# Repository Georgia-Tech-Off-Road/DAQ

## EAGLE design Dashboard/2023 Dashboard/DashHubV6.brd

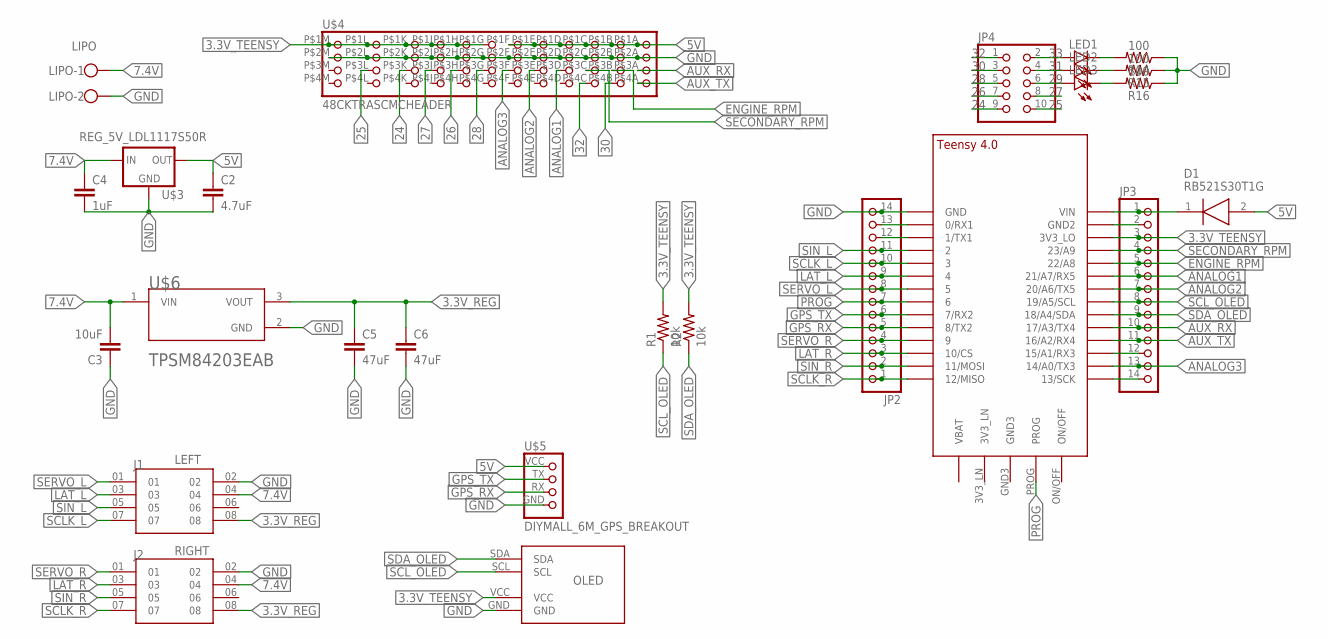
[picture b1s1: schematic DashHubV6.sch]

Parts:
C2: 4.7uF; C0603
C3: 10uF; C1206
C4: 1uF; C1206
C5, C6: 47uF; C1206
D1: RB521S30T1G; SODFL1608X70N
J1: LEFT; SAMTEC_ESW-104-23-L-D
J2: RIGHT; SAMTEC_ESW-104-23-L-D
JP2, JP3: PINHD-1X14; 1X14
JP4: PINHD-2X5; 2X05
LED1, LED2, LED3: LEDCHIPLED_1206; CHIPLED_1206
LIPO: LIPO; W237-102
R1, R2: 10k; R0603
R14, R15, R16: 100; AXIAL-0.3
U$1: TEENSY_4.0-BASIC
U$2: OLED_SSD1306
U$3: REG_5V_LDL1117S50R; SOT230P700X180-4N
U$4: 48CKTRASCMCHEADER
U$5: DIYMALL_6M_GPS_BREAKOUT
U$6: TPSM84205EAB

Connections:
3.3V_REG: C5.1, C6.1, J1.08, J2.08, U$6.3 (VOUT)
3.3V_TEENSY: JP3.3, R1.2, R2.2, U$1.3V3_LO, U$2.VCC, U$4.P$1G (1G), U$4.P$1H (1H), U$4.P$1J (1J), U$4.P$1K (1K), U$4.P$1L (1L), U$4.P$1M (1M)
5V: C2.1, D1.2 (A), U$3.2 (OUT), U$3.4 (OUT), U$4.P$1A (1A), U$4.P$1B (1B), U$4.P$1C (1C), U$4.P$1D (1D), U$4.P$1E (1E), U$4.P$1F (1F), U$5.VCC
7.4V: C3.2, C4.1, J1.04, J2.04, LIPO.1, U$3.3 (IN), U$6.1 (VIN)
24: JP4.9, U$4.P$3K (3K)
25: JP4.10, U$4.P$3L (3L)
26: JP4.7, U$4.P$3H (3H)
27: JP4.8, U$4.P$3J (3J)
28: JP4.5, U$4.P$3G (3G)
29: JP4.6, LED3.A
30: JP4.3, U$4.P$4B (4B)
31: JP4.4, LED2.A
32: JP4.1, U$4.P$4C (4C)
33: JP4.2, LED1.A
ANALOG1: JP3.6, U$1.21/A7 (21/A7/RX5), U$4.P$3D (3D)
ANALOG2: JP3.7, U$1.20/A6 (20/A6/TX5), U$4.P$3E (3E)
ANALOG3: JP3.13, U$1.14/A0 (14/A0/TX3), U$4.P$3F (3F)
AUX_RX: JP3.10, U$1.17/A3 (17/A3/TX4), U$4.P$3A (3A)
AUX_TX: JP3.11, U$1.16/A2 (16/A2/RX4), U$4.P$4A (4A)
CURR_SENSE: JP3.12, U$1.15/A1 (15/A1/RX3)
ENGINE_RPM: JP3.5, U$1.22/A8, U$4.P$3B (3B)
GND: C2.2, C3.1, C4.2, C5.2, C6.2, J1.02, J2.02, JP2.14, LIPO.2, R14.P$1 (1), R15.P$1 (1), R16.P$1 (1), U$1.GND, U$2.GND, U$3.1 (GND), U$4.P$2A (2A), U$4.P$2B (2B), U$4.P$2C (2C), U$4.P$2D (2D), U$4.P$2E (2E), U$4.P$2F (2F), U$4.P$2G (2G), U$4.P$2H (2H), U$4.P$2J (2J), U$4.P$2K (2K), U$4.P$2L (2L), U$4.P$2M (2M), U$5.GND, U$6.2 (GND)
GND2: JP3.2, U$1.GND2
GPS_RX: JP2.5, U$1.8 (8/TX2), U$5.RX
GPS_TX: JP2.6, U$1.7 (7/RX2), U$5.TX
LAT_L: J1.03, JP2.9, U$1.4/CANRX (4)
LAT_R: J2.03, JP2.3, U$1.10/CS
unnamed: D1.1 (K), JP3.1, U$1.VIN
unnamed: LED1.C, R14.P$2 (2)
unnamed: LED2.C, R15.P$2 (2)
unnamed: LED3.C, R16.P$2 (2)
PROG: JP2.7, U$1.6, U$1.PROG
SCLK_D: JP3.14, U$1.13/SCK
SCLK_L: J1.07, JP2.10, U$1.3/CANTX (3)
SCLK_R: J2.07, JP2.1, U$1.12/MISO
SCL_OLED: JP3.8, R1.1, U$1.19/A5/SCL, U$2.SCL
SDA_OLED: JP3.9, R2.1, U$1.18/A4/SDA, U$2.SDA
SECONDARY_RPM: JP3.4, U$1.23/A9, U$4.P$3C (3C)
SERVO_L: J1.01, JP2.8, U$1.5
SERVO_R: J2.01, JP2.4, U$1.9/CS (9)
SIN_L: J1.05, JP2.11, U$1.2
SIN_R: J2.05, JP2.2, U$1.11/MOSI
XBEE_RX: JP2.12, U$1.1/TX (1/TX1)
XBEE_TX: JP2.13, U$1.0/RX (0/RX1)

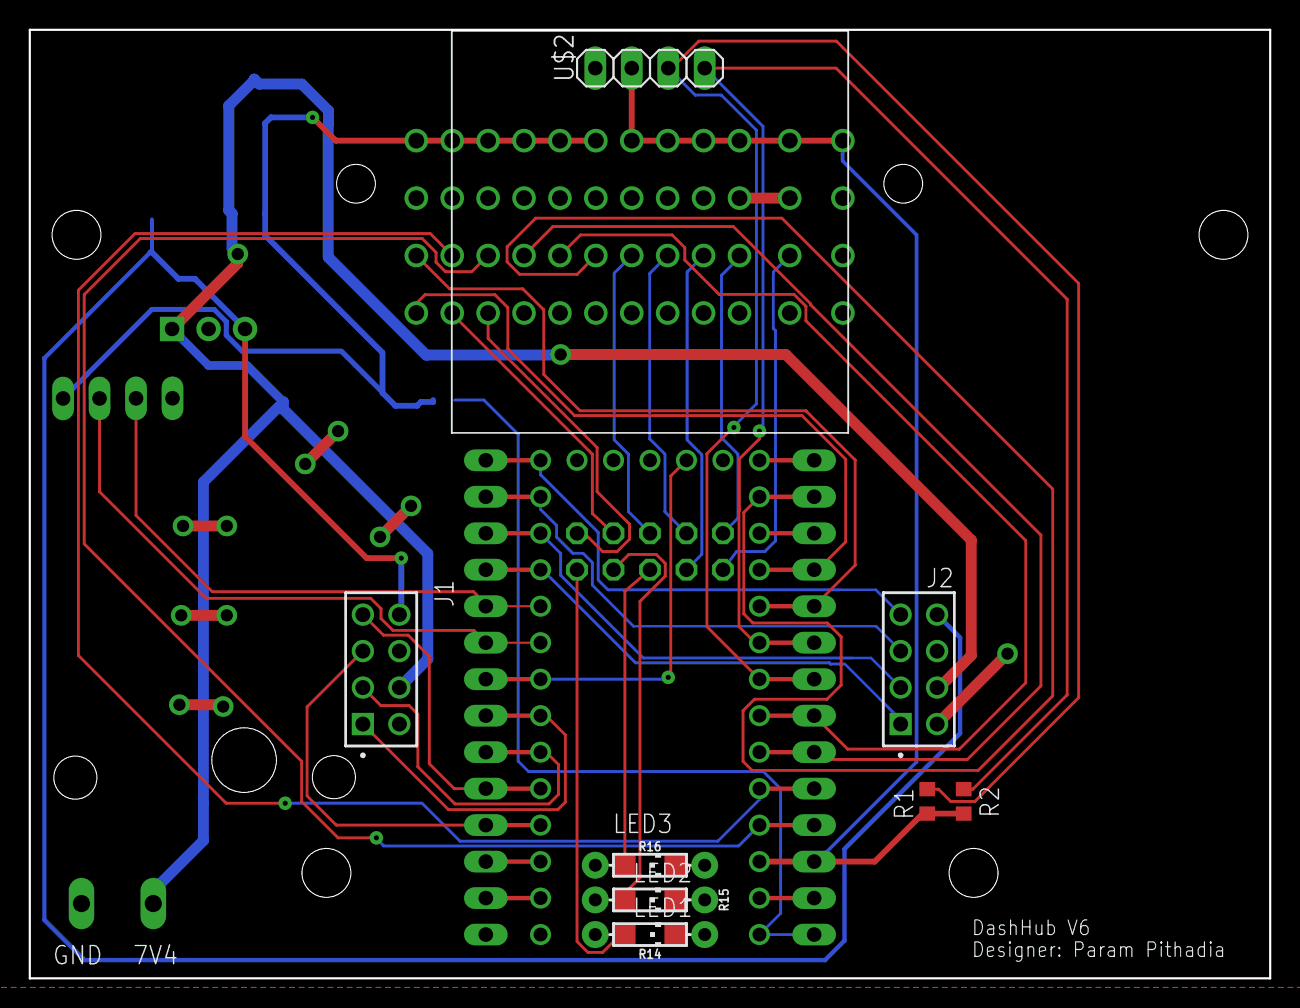
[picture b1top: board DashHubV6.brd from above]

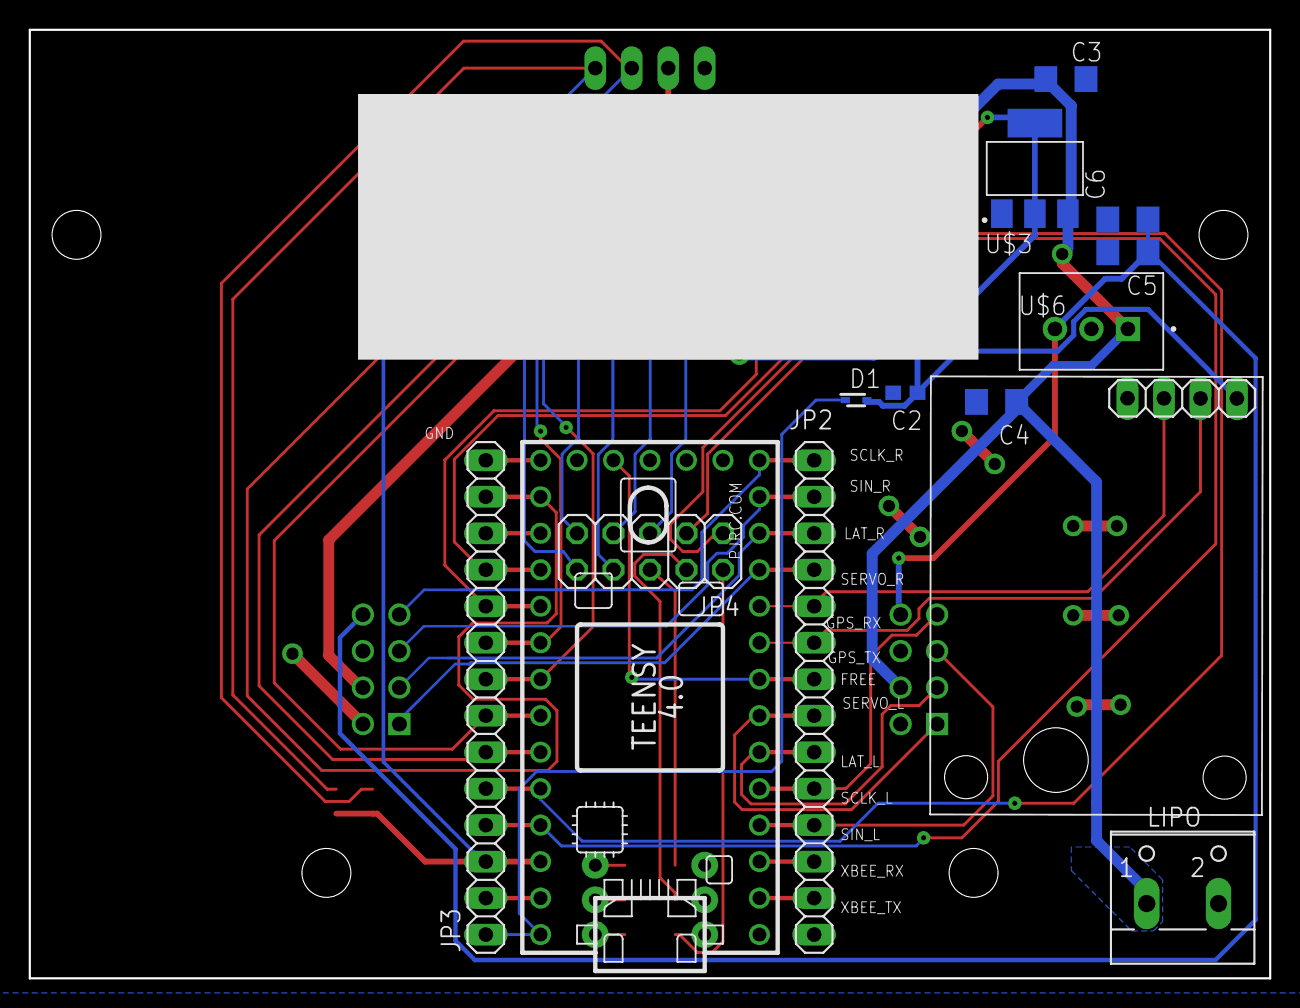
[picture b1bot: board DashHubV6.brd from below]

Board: 2 copper layers, 86.4 x 66.0 mm, 26 parts (15 on the bottom side), 44 nets.

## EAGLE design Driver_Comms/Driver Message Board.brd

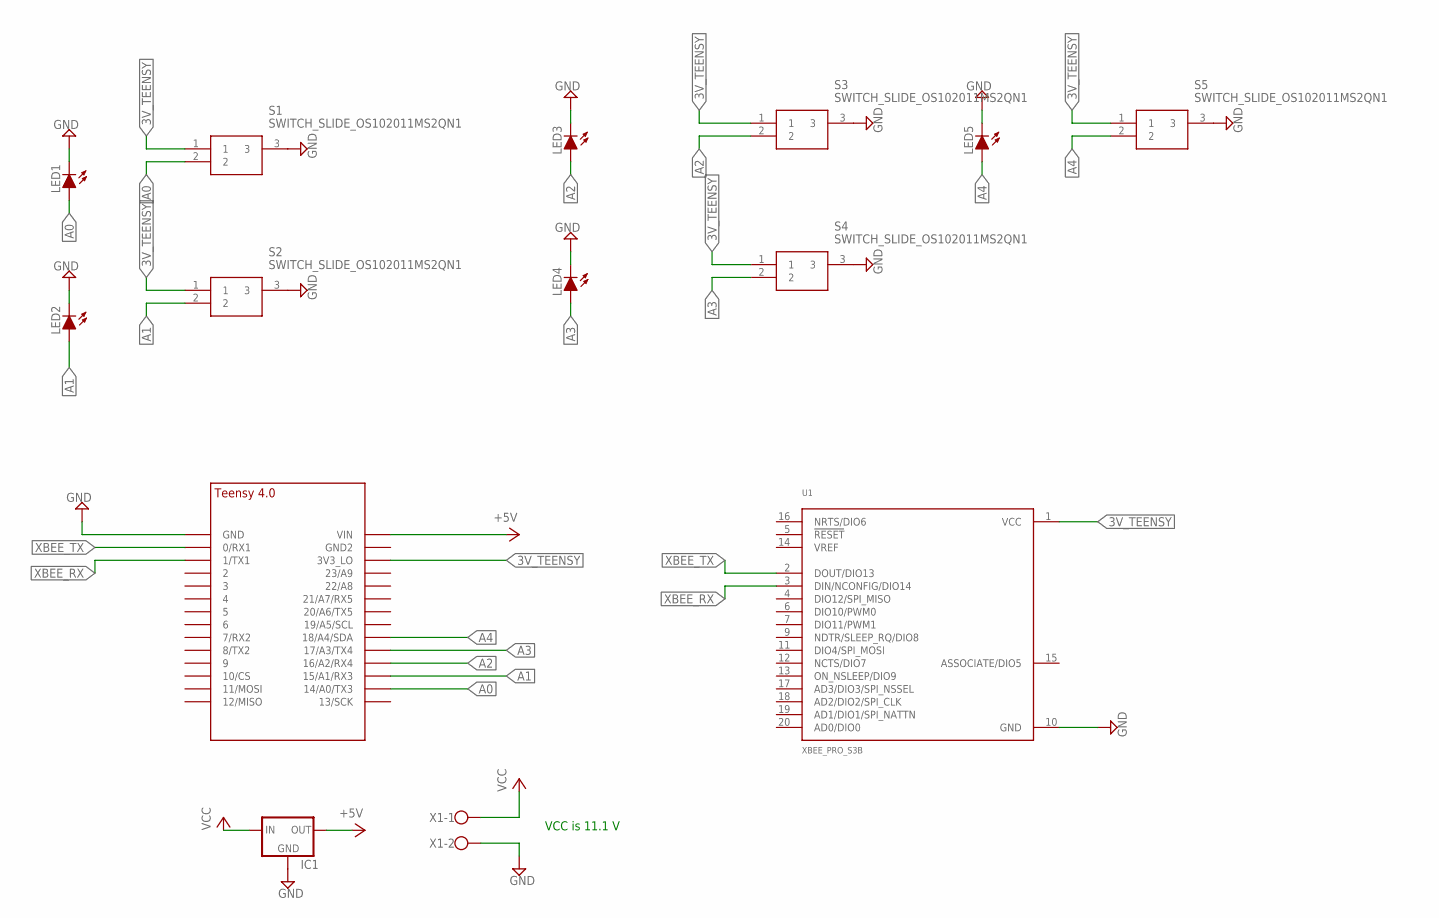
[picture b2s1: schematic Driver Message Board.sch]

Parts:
IC1: REG_5V_L7805_HOR_HOLE; TO-220-H-HOLE
LED1, LED2, LED3, LED4, LED5: LED-5MM
S1, S2, S3, S4, S5: SWITCH_SLIDE_OS102011MS2QN1; OS102011MA1QN1
U1: XBEE_PRO_S3B
U$1: TEENSY_4.0_SIMPLE
X1: W237-102

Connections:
3V_TEENSY: S1.1, S2.1, S3.1, S4.1, S5.1, U1.1 (VCC), U$1.3V3_LO
+5V: IC1.3 (OUT), U$1.VIN
A0: LED1.A, S1.2, U$1.14/A0 (14/A0/TX3)
A1: LED2.A, S2.2, U$1.15/A1 (15/A1/RX3)
A2: LED3.A, S3.2, U$1.16/A2 (16/A2/RX4)
A3: LED4.A, S4.2, U$1.17/A3 (17/A3/TX4)
A4: LED5.A, S5.2, U$1.18/A4/SDA
GND: IC1.2 (GND), LED1.K (C), LED2.K (C), LED3.K (C), LED4.K (C), LED5.K (C), S1.3, S2.3, S3.3, S4.3, S5.3, U1.10 (GND), U$1.GND, X1.2
VCC: IC1.1 (IN), X1.1
XBEE_RX: U1.3 (DIN/NCONFIG/DIO14), U$1.1/TX (1/TX1)
XBEE_TX: U1.2 (DOUT/DIO13), U$1.0/RX (0/RX1)

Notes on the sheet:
VCC is 11.1 V

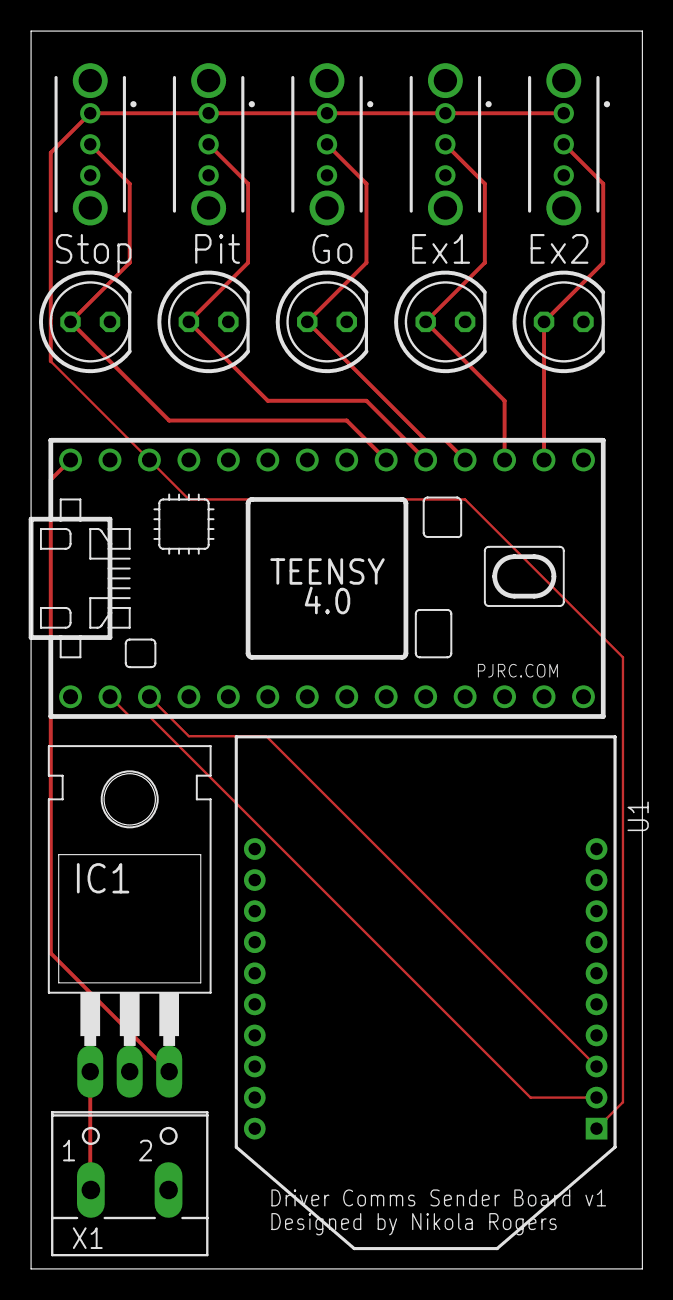
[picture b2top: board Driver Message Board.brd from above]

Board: 2 copper layers, 39.4 x 79.7 mm, 14 parts (0 on the bottom side), 11 nets.

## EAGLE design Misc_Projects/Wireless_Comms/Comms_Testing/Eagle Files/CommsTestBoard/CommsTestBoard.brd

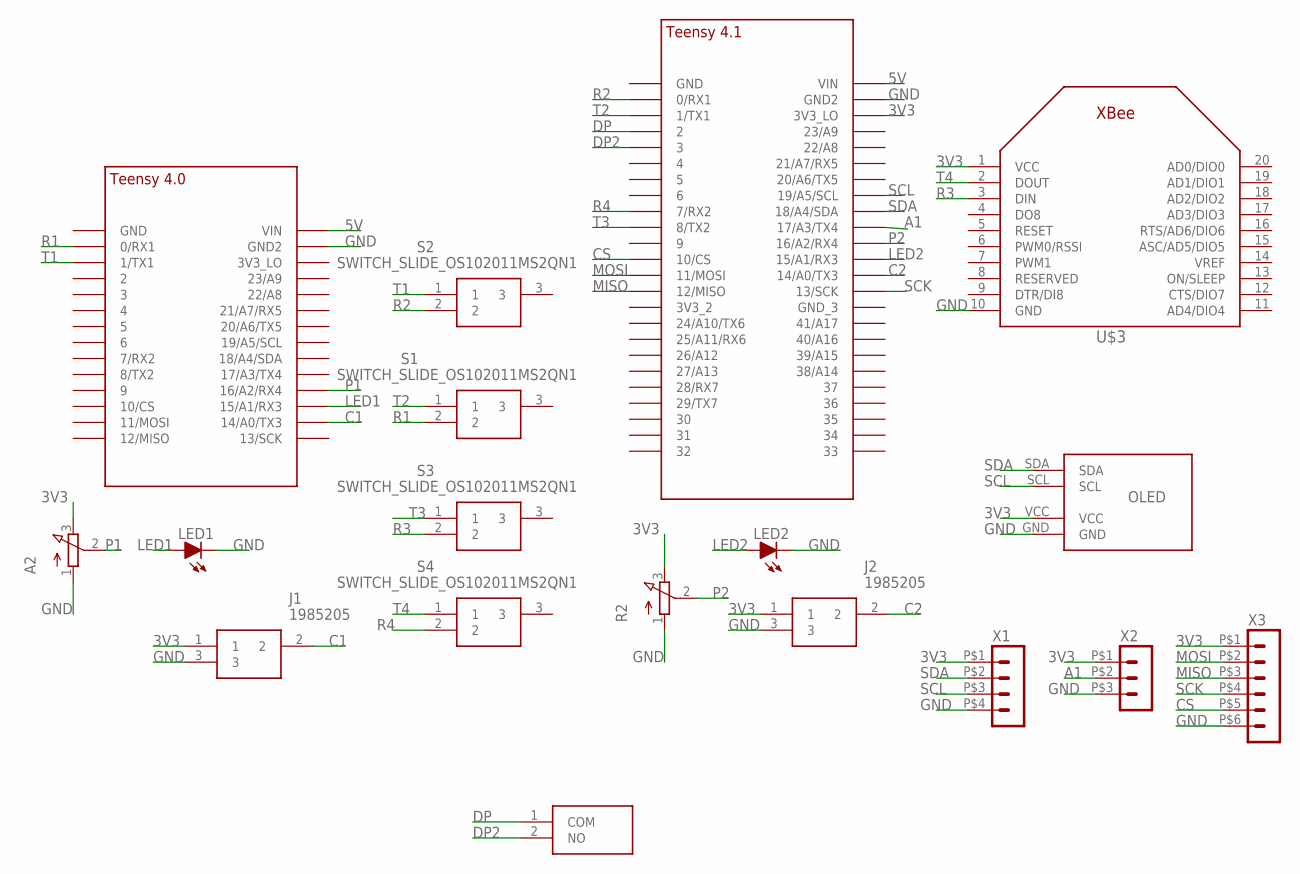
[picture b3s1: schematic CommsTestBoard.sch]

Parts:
A2: POTENTIOMETER; 3RP/1610N
J1, J2: 1985205
LED1, LED2: LED-5MM
R2: POTENTIOMETER; 3RP/1610N
S1, S2, S3, S4: SWITCH_SLIDE_OS102011MS2QN1; OS102011MA1QN1
S5: PTS636_SL50_LFS; PTS636SL50LFS
U$1: TEENSY_4.0_SIMPLE
U$2: TEENSY_4.1_SIMPLE
U$3: XBEE
U$4: OLED_SSD1306
X1: HEADER_POS4_43045-0401; 43045-0400
X2: HEADER_POS3_43650-0300; 43650-0300
X3: HEADER_POS6_43045-0600; 43045-0600

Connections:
3V3: A2.3 (E), J1.1, J2.1, R2.3 (E), U$2.3V3_LO, U$3.1 (VCC), U$4.VCC, X1.P$1 (1), X2.P$1 (1), X3.P$1 (1)
5V: U$1.VIN, U$2.VIN
A1: U$2.17/A3 (17/A3/TX4), X2.P$2 (2)
C1: J1.2, U$1.14/A0 (14/A0/TX3)
C2: J2.2, U$2.14/A0 (14/A0/TX3)
CS: U$2.10/CS, X3.P$5 (5)
DP: S5.1 (COM), U$2.2
DP2: S5.2 (NO), U$2.3/CANTX (3)
GND: A2.1 (A), J1.3, J2.3, LED1.K (C), LED2.K (C), R2.1 (A), U$1.GND2, U$2.GND2, U$3.10 (GND), U$4.GND, X1.P$4 (4), X2.P$3 (3), X3.P$6 (6)
LED1: LED1.A, U$1.15/A1 (15/A1/RX3)
LED2: LED2.A, U$2.15/A1 (15/A1/RX3)
MISO: U$2.12/MISO, X3.P$3 (3)
MOSI: U$2.11/MOSI, X3.P$2 (2)
P1: A2.2 (S), U$1.16/A2 (16/A2/RX4)
P2: R2.2 (S), U$2.16/A2 (16/A2/RX4)
R1: S1.2, U$1.0/RX (0/RX1)
R2: S2.2, U$2.0/RX (0/RX1)
R3: S3.2, U$3.3 (DIN)
R4: S4.2, U$2.7 (7/RX2)
SCK: U$2.13/SCK, X3.P$4 (4)
SCL: U$2.19/A5/SCL, U$4.SCL, X1.P$3 (3)
SDA: U$2.18/A4/SDA, U$4.SDA, X1.P$2 (2)
T1: S2.1, U$1.1/TX (1/TX1)
T2: S1.1, U$2.1/TX (1/TX1)
T3: S3.1, U$2.8 (8/TX2)
T4: S4.1, U$3.2 (DOUT)

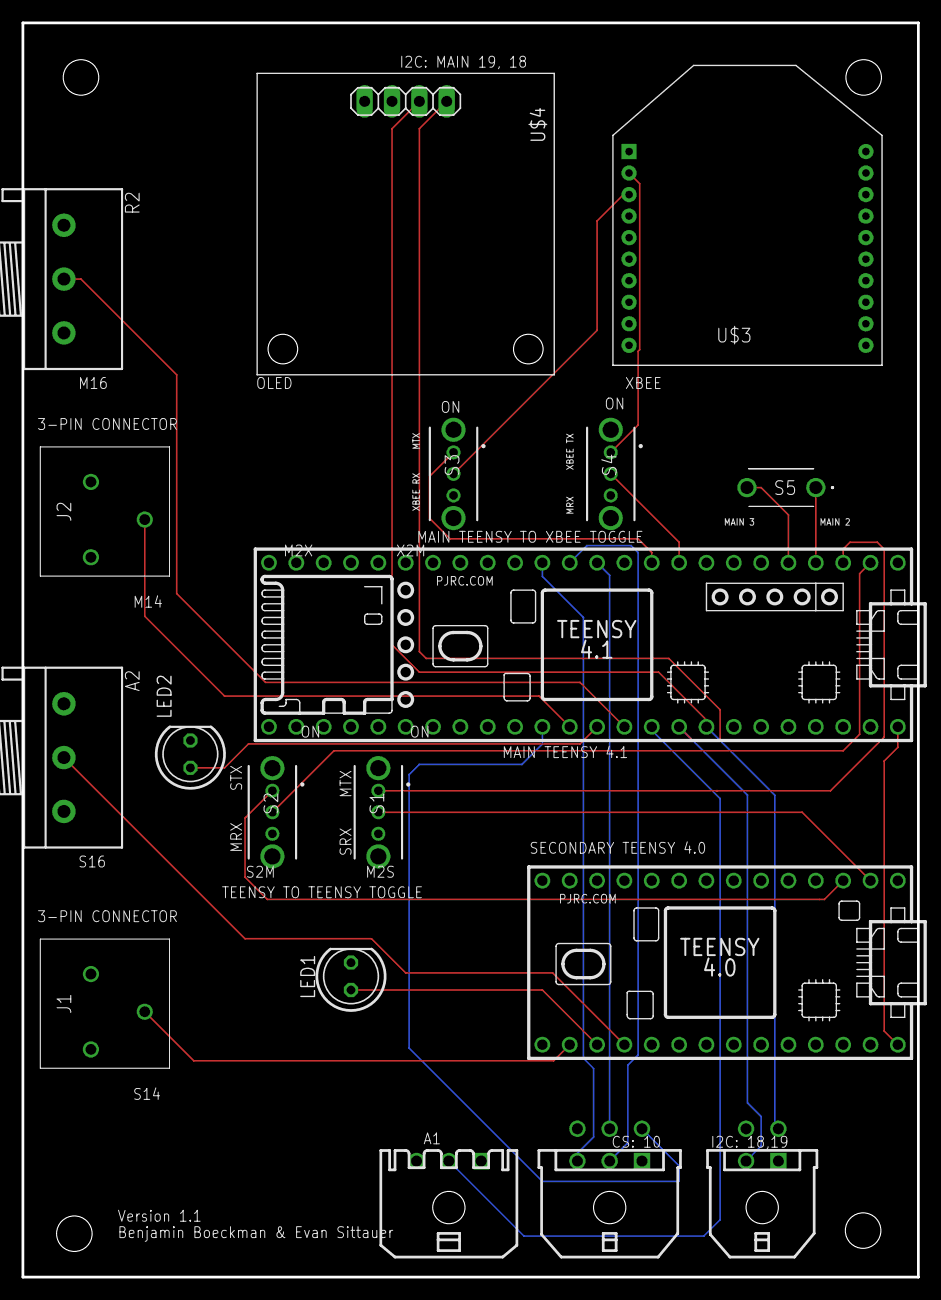
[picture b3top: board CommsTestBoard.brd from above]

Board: 2 copper layers, 83.2 x 116.5 mm, 18 parts (0 on the bottom side), 26 nets.

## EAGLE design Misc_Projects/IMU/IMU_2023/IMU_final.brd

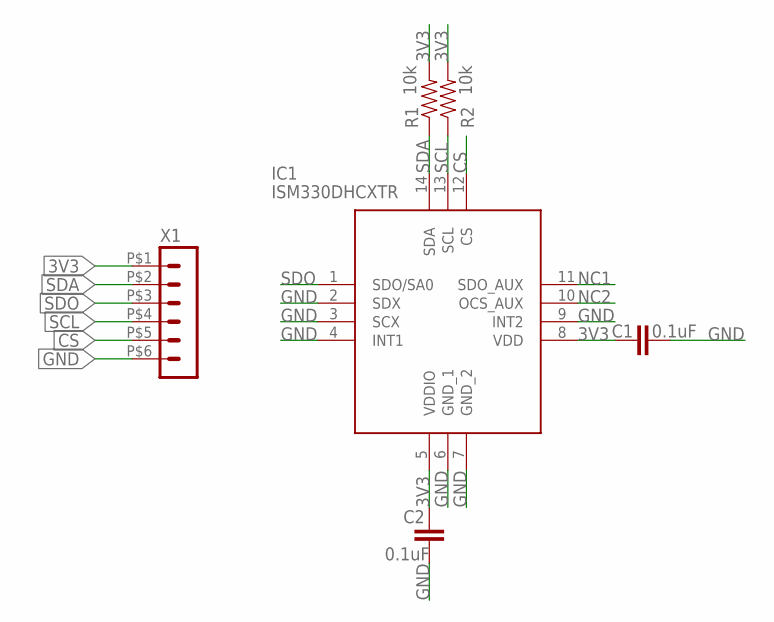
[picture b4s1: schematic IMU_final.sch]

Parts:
C1, C2: 0.1uF; 0603
IC1: ISM330DHCXTR; LGA-14(2.5X3X0.86)
R1, R2: 10k; 0603
X1: HEADER_POS6_43045-0600; 43045-0600

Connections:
3V3: C1.1, C2.1, IC1.5 (VDDIO), IC1.8 (VDD), R1.2, R2.2, X1.P$1 (1)
CS: IC1.12 (CS), X1.P$5 (5)
GND: C1.2, C2.2, IC1.2 (SDX), IC1.3 (SCX), IC1.4 (INT1), IC1.6 (GND_1), IC1.7 (GND_2), IC1.9 (INT2), X1.P$6 (6)
NC1: IC1.11 (SDO_AUX)
NC2: IC1.10 (OCS_AUX)
SCL: IC1.13 (SCL), R2.1, X1.P$4 (4)
SDA: IC1.14 (SDA), R1.1, X1.P$2 (2)
SDO: IC1.1 (SDO/SA0), X1.P$3 (3)

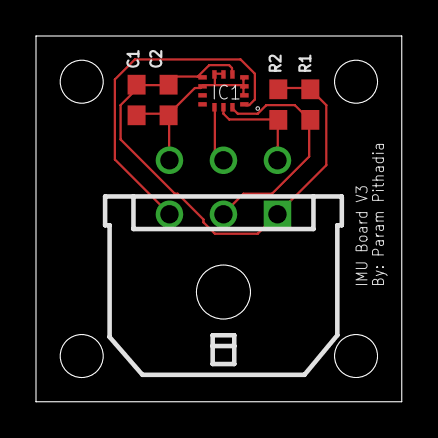
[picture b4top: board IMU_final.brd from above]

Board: 2 copper layers, 20.3 x 20.3 mm, 6 parts (0 on the bottom side), 6 nets.

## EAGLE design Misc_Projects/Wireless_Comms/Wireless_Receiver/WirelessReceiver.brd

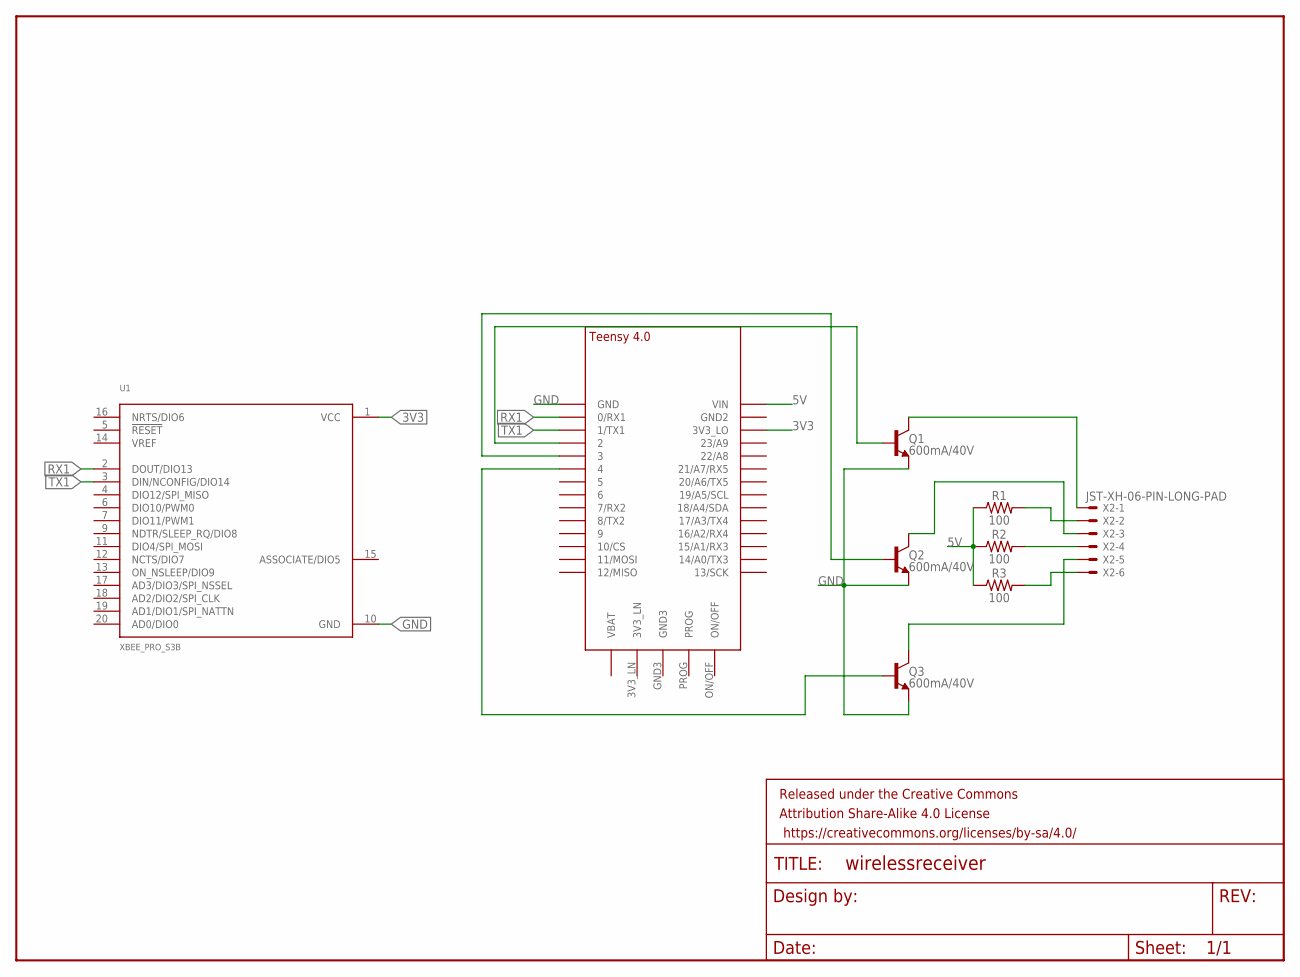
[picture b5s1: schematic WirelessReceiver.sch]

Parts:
FRAME1: FRAME-LETTERNO_PACKAGE; DUMMY
Q1, Q2, Q3: 600mA/40V; SOT23-3
R1, R2, R3: 100; AXIAL-0.3
U1: XBEE_PRO_S3B
U$1: TEENSY_4.0-BASIC
X2: JST-XH-06-PIN-LONG-PAD; JST-XH-06-PACKAGE-LONG-PAD

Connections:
3V3: U1.1 (VCC), U$1.3V3_LO
5V: R1.P$1 (1), R2.P$1 (1), R3.P$1 (1), U$1.VIN
GND: Q1.2 (E), Q2.2 (E), Q3.2 (E), U1.10 (GND), U$1.GND
unnamed: R1.P$2 (2), X2.2
unnamed: R2.P$2 (2), X2.4
unnamed: R3.P$2 (2), X2.6
unnamed: Q1.3 (C), X2.1
unnamed: Q2.3 (C), X2.3
unnamed: Q3.3 (C), X2.5
unnamed: Q1.1 (B), U$1.2
unnamed: Q2.1 (B), U$1.3/CANTX (3)
unnamed: Q3.1 (B), U$1.4/CANRX (4)
RX1: U1.2 (DOUT/DIO13), U$1.0/RX (0/RX1)
TX1: U1.3 (DIN/NCONFIG/DIO14), U$1.1/TX (1/TX1)

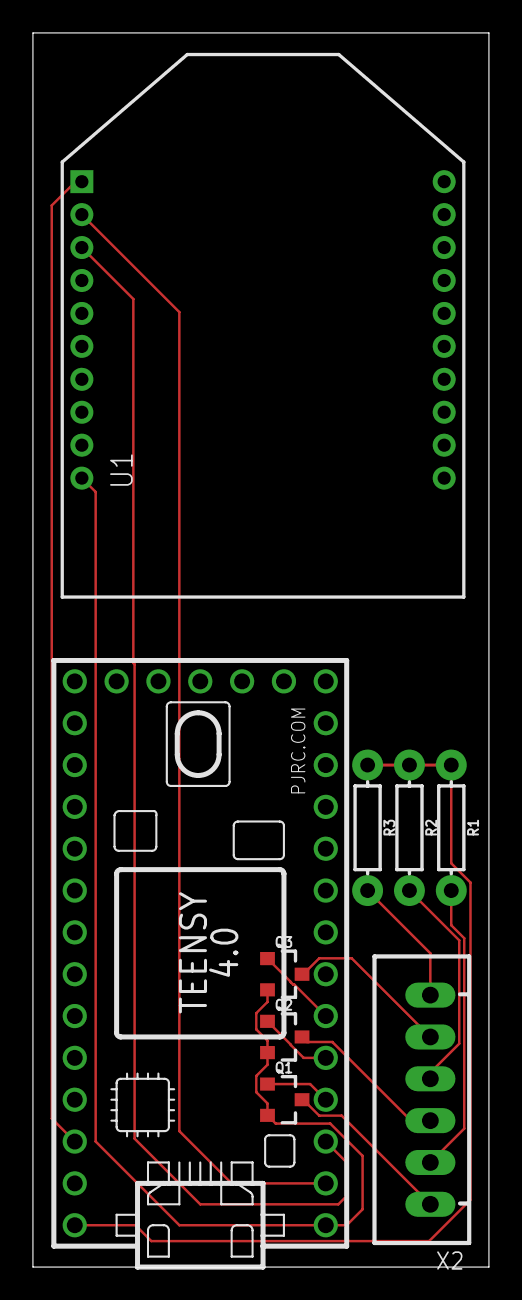
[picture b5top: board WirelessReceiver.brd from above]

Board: 2 copper layers, 27.7 x 74.9 mm, 10 parts (0 on the bottom side), 14 nets.

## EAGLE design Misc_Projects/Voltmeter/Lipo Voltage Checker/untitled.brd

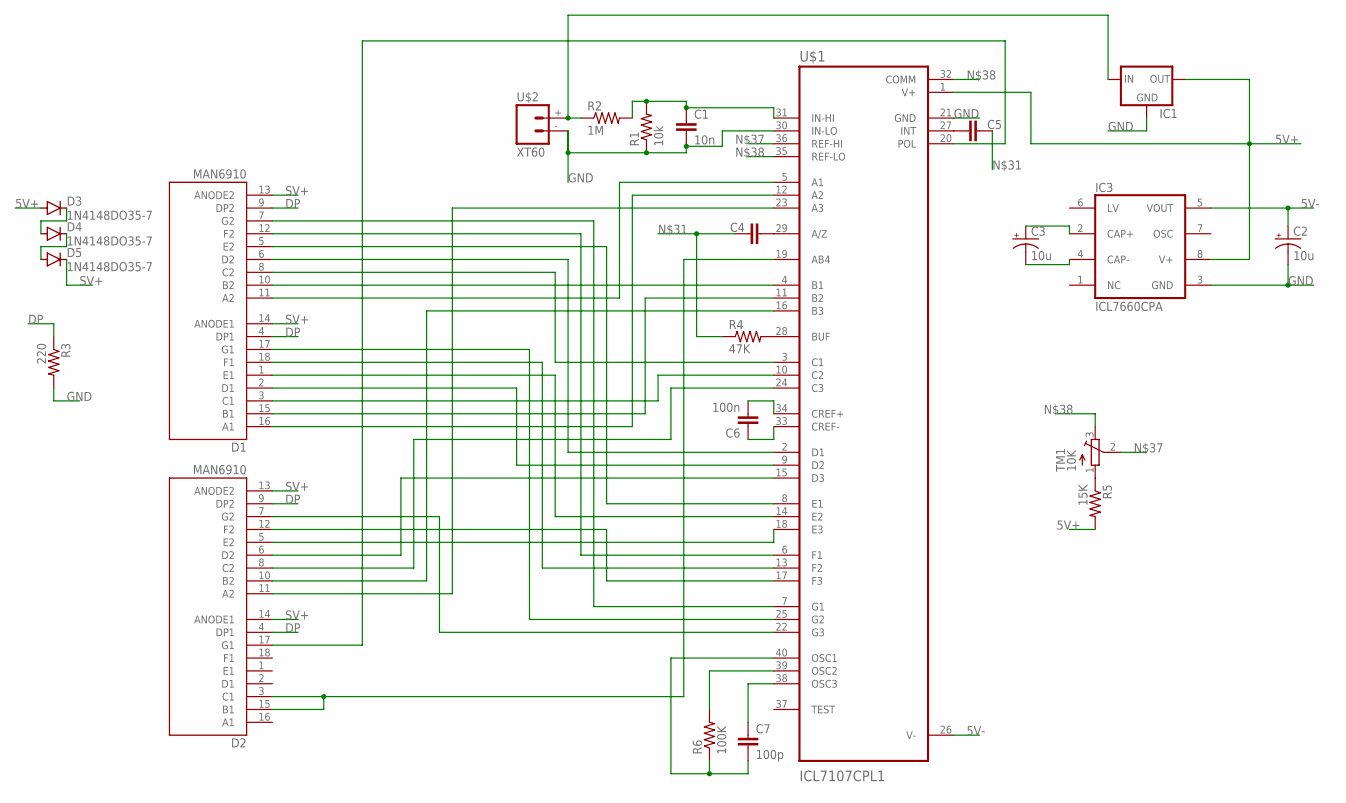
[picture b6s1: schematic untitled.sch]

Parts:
C1: 10n; CAP-PTH-SMALL-KIT
C2, C3: 10u; E2-5
C4, C5: CAPKIT; CAP-PTH-SMALL-KIT
C6: 100n; CAP-PTH-SMALL-KIT
C7: 100p; CAP-PTH-SMALL-KIT
D1, D2: MAN6910; DIP1524W51P254L2503H810Q18
D3, D4, D5: 1N4148DO35-7; DO35-7
IC1: REG_5V_L7805_HOR; TO-220-H
IC3: ICL7660CPA; DIL08
R1: 10k; 1/2W-0.5
R2: 1M; 1/2W-0.5
R3: 220; 1/2W-0.5
R4: 47K; 1/2W-0.5
R5: 15K; 1/2W-0.5
R6: 100K; 1/2W-0.5
TM1: 10K; TC33X
U$1: ICL7107CPL1; DIP1524W46P254L5271H508Q40
U$2: XT60

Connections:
5V+: D3.A, IC1.3 (OUT), IC3.8 (V+), R5.2, U$1.1 (V+)
5V-: C2.+, IC3.5 (VOUT), U$1.26 (V-)
DP: D1.4 (DP1), D1.9 (DP2), D2.4 (DP1), D2.9 (DP2), R3.1
GND: C1.2, C2.-, IC1.2 (GND), IC3.3 (GND), R1.1, R3.2, U$1.21 (GND), U$1.30 (IN-LO), U$2.- (1)
unnamed: C3.+, IC3.2 (CAP+)
unnamed: R4.2, U$1.28 (BUF)
unnamed: D3.C, D4.A
unnamed: C1.1, R1.2, R2.2, U$1.31 (IN-HI)
unnamed: C3.-, IC3.4 (CAP-)
unnamed: D4.C, D5.A
unnamed: D1.3 (C1), U$1.10 (C2)
unnamed: D1.6 (D2), U$1.2 (D1)
unnamed: D1.8 (C2), U$1.3 (C1)
unnamed: D1.10 (B2), U$1.4 (B1)
unnamed: D1.11 (A2), U$1.5 (A1)
unnamed: D1.5 (E2), U$1.8 (E1)
unnamed: D1.12 (F2), U$1.6 (F1)
unnamed: D1.7 (G2), U$1.7 (G1)
unnamed: D1.2 (D1), U$1.9 (D2)
unnamed: D1.15 (B1), U$1.11 (B2)
unnamed: D1.16 (A1), U$1.12 (A2)
unnamed: D1.1 (E1), U$1.14 (E2)
unnamed: D1.18 (F1), U$1.13 (F2)
unnamed: D1.17 (G1), U$1.25 (G2)
unnamed: D2.6 (D2), U$1.15 (D3)
unnamed: D2.10 (B2), U$1.16 (B3)
unnamed: D2.12 (F2), U$1.17 (F3)
unnamed: D2.5 (E2), U$1.18 (E3)
unnamed: D2.8 (C2), U$1.24 (C3)
unnamed: D2.11 (A2), U$1.23 (A3)
unnamed: D2.7 (G2), U$1.22 (G3)
unnamed: D2.3 (C1), D2.15 (B1), U$1.19 (AB4)
unnamed: D2.17 (G1), U$1.20 (POL)
unnamed: C4.2, C5.1, R4.1
unnamed: C4.1, U$1.29 (A/Z)
unnamed: C5.2, U$1.27 (INT)
unnamed: C6.2, U$1.34 (CREF+)
unnamed: C6.1, U$1.33 (CREF-)
unnamed: R5.1, TM1.1 (A)
unnamed: TM1.2 (S), U$1.36 (REF-HI)
unnamed: TM1.3 (E), U$1.32 (COMM), U$1.35 (REF-LO)
unnamed: R6.2, U$1.39 (OSC2)
unnamed: C7.1, U$1.38 (OSC3)
unnamed: C7.2, R6.1, U$1.40 (OSC1)
SV+: D1.13 (ANODE2), D1.14 (ANODE1), D2.13 (ANODE2), D2.14 (ANODE1), D5.C
VBAT: IC1.1 (IN), R2.1, U$2.+ (2)

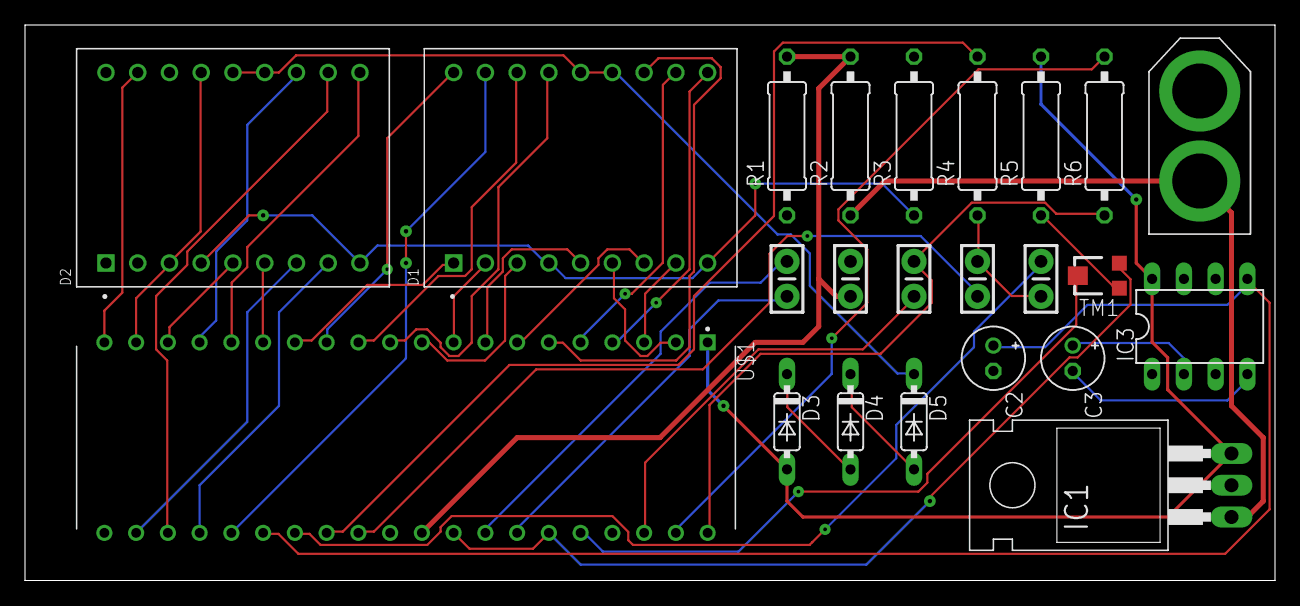
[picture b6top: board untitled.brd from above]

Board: 2 copper layers, 100.0 x 44.4 mm, 23 parts (0 on the bottom side), 46 nets.

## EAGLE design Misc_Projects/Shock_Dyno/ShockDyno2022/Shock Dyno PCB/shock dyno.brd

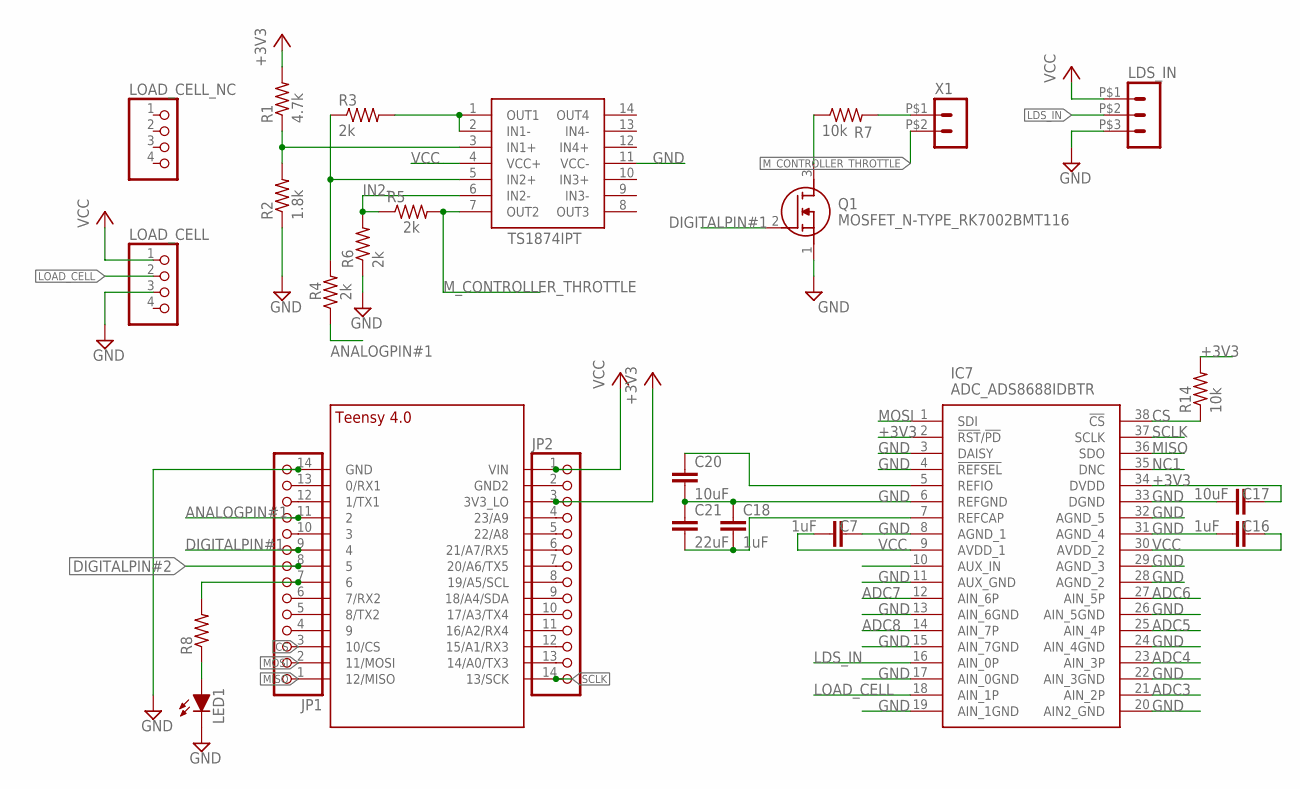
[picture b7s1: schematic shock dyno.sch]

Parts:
C7, C16, C18: 1uF; C0603
C17: 10uF; C0603
C20: 10uF; C0805
C21: 22uF; C1210
IC7: ADC_ADS8688IDBTR; SOP50P640X120-38N
JP1, JP2: PINHD-1X14; 1X14
LDS_IN: HEADER_POS3_43650-0300; 43650-0300
LED1: LED-5MM
LOAD_CELL: PINHD-1X4; 1X04
LOAD_CELL_NC: PINHD-1X4; 1X04
Q1: MOSFET_N-TYPE_RK7002BMT116; BSS64AHZGT116
R1: 4.7k; R0603
R2: 1.8k; R0603
R3, R4, R5, R6: 2k; R0603
R7, R14: 10k; R0603
R8: RES_SMDR0603; R0603
U$1: TS1874IPT; TSSOP14
U$2: TEENSY_4.0_SIMPLE
X1: HEADER_POS2_43650-0200; 43650-0200

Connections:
+3V3: C17.1, IC7.2 (!RST!/!PD), IC7.34 (DVDD), JP2.3, R1.2, R14.2, U$2.3V3_LO
ADC3: IC7.21 (AIN_2P)
ADC4: IC7.23 (AIN_3P)
ADC5: IC7.25 (AIN_4P)
ADC6: IC7.27 (AIN_5P)
ADC7: IC7.12 (AIN_6P)
ADC8: IC7.14 (AIN_7P)
ANALOGPIN#1: JP1.11, R4.1, U$2.2
CS: IC7.38 (!CS), JP1.3, R14.1, U$2.10/CS
DIGITALPIN#1: JP1.9, Q1.2 (G), U$2.4/CANRX (4)
DIGITALPIN#2: JP1.8, U$2.5
GND: C7.1, C16.2, C17.2, C18.1, C20.2, C21.1, IC7.3 (DAISY), IC7.4 (!REFSEL), IC7.6 (REFGND), IC7.8 (AGND_1), IC7.11 (AUX_GND), IC7.13 (AIN_6GND), IC7.15 (AIN_7GND), IC7.17 (AIN_0GND), IC7.19 (AIN_1GND), IC7.20 (AIN2_GND), IC7.22 (AIN_3GND), IC7.24 (AIN_4GND), IC7.26 (AIN_5GND), IC7.28 (AGND_2), IC7.29 (AGND_3), IC7.31 (AGND_4), IC7.32 (AGND_5), IC7.33 (DGND), JP1.14, LDS_IN.P$3 (3), LED1.K (C), LOAD_CELL.3, Q1.1 (S), R2.1, R6.1, U$1.11 (VCC-), U$2.GND
IN2-: R5.1, R6.2, U$1.6 (IN2-)
LDS_IN: IC7.16 (AIN_0P), LDS_IN.P$2 (2)
LOAD_CELL: IC7.18 (AIN_1P), LOAD_CELL.2
MISO: IC7.36 (SDO), JP1.1, U$2.12/MISO
MOSI: IC7.1 (SDI), JP1.2, U$2.11/MOSI
M_CONTROLLER_THROTTLE: R5.2, U$1.7 (OUT2), X1.P$2 (2)
unnamed: R1.1, R2.2, U$1.3 (IN1+)
unnamed: R3.1, R4.2, U$1.5 (IN2+)
unnamed: R3.2, U$1.1 (OUT1), U$1.2 (IN1-)
unnamed: R7.2, X1.P$1 (1)
unnamed: JP1.4, U$2.9/CS (9)
unnamed: JP1.5, U$2.8 (8/TX2)
unnamed: JP1.10, U$2.3/CANTX (3)
unnamed: JP1.6, U$2.7 (7/RX2)
unnamed: Q1.3 (D), R7.1
unnamed: LED1.A, R8.1
unnamed: JP1.7, R8.2, U$2.6
unnamed: JP1.12, U$2.1/TX (1/TX1)
unnamed: JP1.13, U$2.0/RX (0/RX1)
unnamed: JP2.2, U$2.GND2
unnamed: JP2.4, U$2.23/A9
unnamed: JP2.5, U$2.22/A8
unnamed: JP2.6, U$2.21/A7 (21/A7/RX5)
unnamed: JP2.7, U$2.20/A6 (20/A6/TX5)
unnamed: JP2.8, U$2.19/A5/SCL
unnamed: JP2.9, U$2.18/A4/SDA
unnamed: JP2.10, U$2.17/A3 (17/A3/TX4)
unnamed: JP2.11, U$2.16/A2 (16/A2/RX4)
unnamed: JP2.12, U$2.15/A1 (15/A1/RX3)
unnamed: JP2.13, U$2.14/A0 (14/A0/TX3)
unnamed: C18.2, C21.2, IC7.7 (REFCAP)
unnamed: C20.1, IC7.5 (REFIO)
NC1: IC7.35 (DNC)
SCLK: IC7.37 (SCLK), JP2.14, U$2.13/SCK
VCC: C7.2, C16.1, IC7.9 (AVDD_1), IC7.30 (AVDD_2), JP2.1, LDS_IN.P$1 (1), LOAD_CELL.1, U$1.4 (VCC+), U$2.VIN

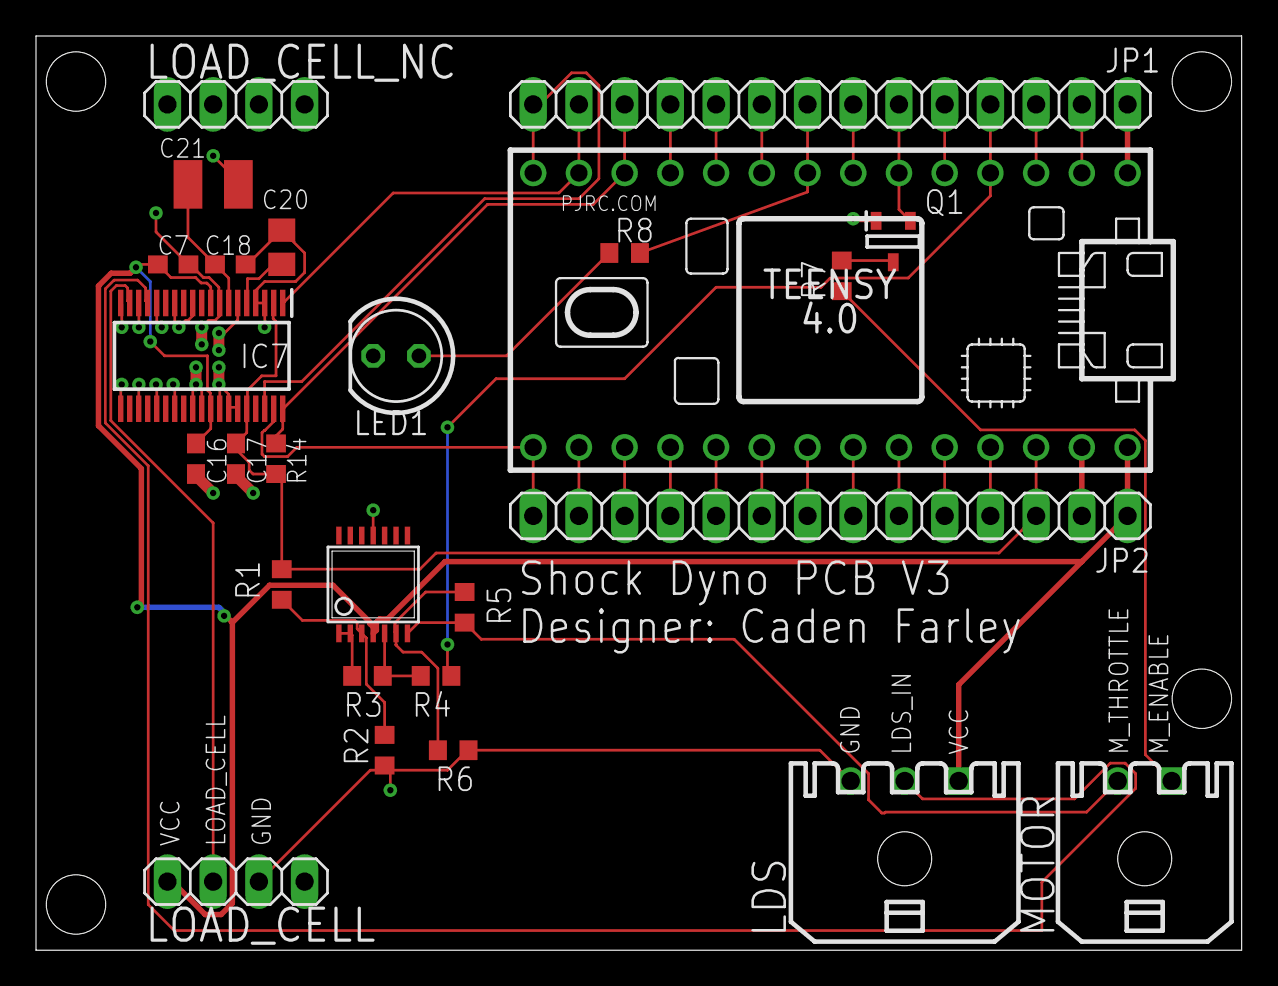
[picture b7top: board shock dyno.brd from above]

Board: 2 copper layers, 67.0 x 50.8 mm, 26 parts (0 on the bottom side), 40 nets.

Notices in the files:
parts and their libraries:
SparkFun-Resistors: Licensing: Creative Commons ShareAlike 4.0 International - https://creativecommons.org/licenses/by-sa/4.0
COPYRIGHT: Copyright (C) 2022 Ultra Librarian. All rights reserved.
SparkFun-Aesthetics: Released under the Creative Commons Attribution Share-Alike 4.0 License
